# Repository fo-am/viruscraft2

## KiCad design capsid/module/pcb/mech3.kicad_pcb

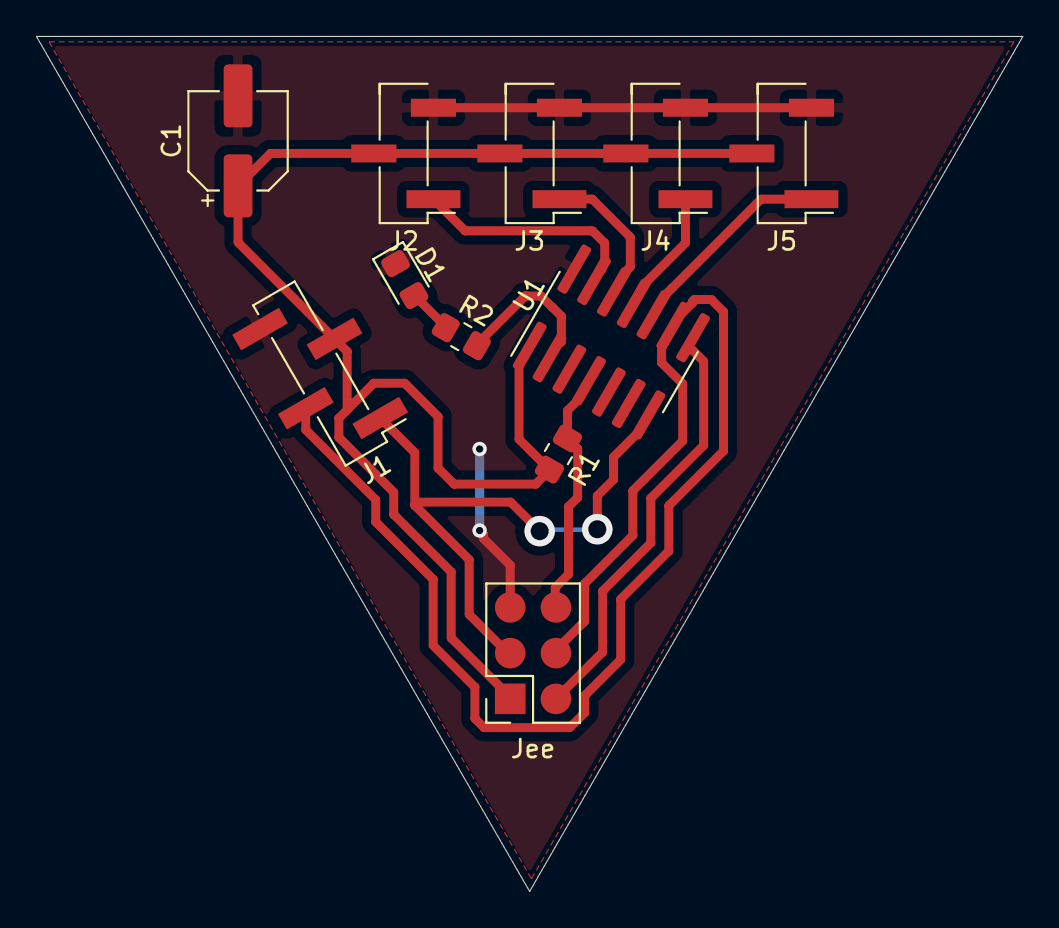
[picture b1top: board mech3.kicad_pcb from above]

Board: 2 copper layers, 54.8 x 47.5 mm, 11 parts (0 on the bottom side), 12 nets.

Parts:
C1: 120uF; CP_Elec_5x5.8
D1: LED; LED_0805_2012Metric_Pad1.15x1.40mm_HandSolder
J1: Conn_01x04_Male; PinHeader_1x04_P2.54mm_Vertical_SMD_Pin1Left
J2, J3, J4, J5: Conn_01x03_Male; PinHeader_1x03_P2.54mm_Vertical_SMD_Pin1Left
Jee: Conn_02x03_Odd_Even; PinSocket_2x03_P2.54mm_Vertical
R1: 10K; R_0805_2012Metric_Pad1.20x1.40mm_HandSolder
R2: 100; R_0805_2012Metric_Pad1.20x1.40mm_HandSolder
U1: ATtiny84A-SSU; SOIC-14_3.9x8.7mm_P1.27mm

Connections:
+5V: C1.1, J1.3, J2.2, J3.2, J4.2, J5.2, Jee.1, R1.2, U1.1
/miso: Jee.2, U1.8
/reset: Jee.6, R1.1, U1.4
/scl: J1.2, Jee.4, U1.9
/sda: J1.1, Jee.3, U1.7
/servo_a: J2.1, U1.13
/servo_b: J3.1, U1.12
/servo_c: J4.1, U1.11
/servo_d: J5.1, U1.10
Earth: C1.2, D1.1, J1.4, J2.3, J3.3, J4.3, J5.3, Jee.5, U1.14
unnamed: D1.2, R2.1
unnamed: R2.2, U1.2

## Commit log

2020-10-20 first commit - working avr servo controller
2020-10-20 added arduino prototype
2020-10-20 rename
2020-10-20 mess
2020-10-20 added mech design
2020-10-23 new registers
2020-12-01 working version on PCB
2020-12-01 update kicad files
2021-01-12 new game code started
2021-01-12 removed old screenshots
2021-01-14 added hosts and fluid sim
2021-01-15 basic infection
2021-01-16 swapped virus host ownership so the host takes control of the virus when it's infected
2021-01-18 random optimisations
2021-01-20 first playable version
2021-01-21 made more playable, and a bit hard
2021-01-21 text
2021-02-10 micro viruses
2021-02-18 added levels to the game
2021-02-22 levels added and tuned
2021-02-22 params from browser
2021-02-23 added mutation game
2021-02-25 three receptors, tuning and fixes
2021-03-09 new host images, refactor to support multiple variants
2021-03-09 two new stages added
2021-03-09 hosts move better, levels balanced
2021-03-10 new host frames
2021-03-11 fixed host anim sequence and started stage implementation
2021-03-11 fading hosts
2021-03-11 small fix
2021-03-11 loading params fix
2021-03-11 maybe fix
2021-03-29 big commit with new host animations, receptors and viruses
2021-03-29 styling
2021-04-01 firmware improvements and working with dfrobot servos
2021-04-08 added arduino code and new mutator buttons
2021-04-08 buttons link to receptor mixer
2021-04-08 mixer now controls mutator button levels
2021-04-08 mixer behaves more as expected
2021-04-08 dice working
2021-04-08 dice better anim
2021-04-08 tweaks and simplifications - made the mutation just random, not a 50% chance of changing a receptor
2021-04-08 added favicon
2021-04-10 added a scoring system and hints
2021-04-10 only one tip at a time!
2021-04-10 added help bubbles - no actual help yet tho
2021-04-12 added servo driver
2021-04-12 added bad sensor code
2021-04-12 added non-debug params mode Fixed: #11
2021-04-12 jigging around the draw order and added lives Fixed: #17
2021-04-13 linked stages and levels together Fixed: #4
2021-04-13 text bg Fixed: #25
2021-04-13 removed mutation countdown when it's not gonna happen before the level ind Fixed: #21
2021-04-13 Increased grace amount of hosts before infection can occur to 3 Fixed: #24
2021-04-13 started score saving and server work Fixed: #28 Fixed: #27
2021-04-13 sorted scoring, database and leaderboard Fixed: #29 Fixed: #6
2021-04-13 turned off cheat
2021-04-13 added missing help bubbles
2021-04-13 loading text col
2021-04-13 nuking old local parameters
2021-04-14 swapped multivariant mutator for the shape buttons Fixed: #33
2021-04-15 added help for first stage Fixed: #32 Fixed: #22
2021-04-15 help fix
2021-04-15 more help text
2021-04-15 Fixed: #31
2021-04-27 6 triangles working
2021-05-07 added calibration to the capsid driver and tested a load of servos
2021-05-07 tested new pcb and added power control to the driver
2021-05-10 added server for robot control
2021-05-10 game now talks to the robot
2021-05-12 all triangle test & added auto reboot
2021-05-13 virus WORKING, added crc checks and fine tuning timing
2021-05-13 firmware updates, watchdog timers, crc checking, brownout fuse set...
2021-05-20 added auto detection, crc and everything to shape server
2021-05-20 new calibration to stop it overpowering, and a lot of tweaking
2021-05-21 page navigation and structure expanded - Fixed: #48
2021-05-21 new buttons added Fixed: #46
2021-05-21 help bubbles now use highlight col
2021-05-21 added question marks to virus in hidden game: Fixed: #40 Fixed: #1
2021-05-21 sprites now have 1 pixel overlap, seems to help with joins - Fixed: #41
2021-05-21 another 1 pixel overlap fix
2021-05-21 added demo hosts
2021-05-24 added viruses to the demo - Fixed: #11
2021-05-24 added sensor hardware
2021-05-24 added cheat mode
2021-05-26 new IP addr
2021-05-26 added sensor websocket thingy and tests all working
2021-05-27 fixed demo problem when not registered, and reordered buttons
2021-05-27 sorting out installation-version
2021-06-04 added about text, game over condition, added game end screen, added score for ranking Fixed: #30
2021-06-04 leaderboard and end game sorted
2021-06-04 fixed play again button
2021-06-04 added arrow to help boxes Fixed: #50
2021-06-04 more help bubbles Fixed: #43 Fixed: #36
2021-06-04 loads more tips, and more positive when doing well! Fixed: #42
2021-06-04 added decent about (first pass) Fixed: #39 Fixed: #8
2021-06-04 added bens stuff Fixed: #64
2021-06-04 added logos Fixed: #63
2021-06-04 bumped params version just in case
2021-06-04 cleaned up keyboard
2021-06-04 full o typos
2021-06-04 simplified results page - Fixed: #71
2021-06-04 fixed/clamped host turning Fixed: #68
2021-06-04 made demo virus a bit smaller Fixed: #67
2021-06-04 banners and pluralising Fixed: #70
2021-06-04 fixed end game thing and turned off cheating
2021-06-04 quit help button tweak Fixed: #72
2021-06-18 added sounds
2021-06-21 server ip address now fixed
2021-06-23 installation mode setup Fixed: #57
2021-06-24 added end of stage text Fixed: #78
2021-06-24 added apostrophe Fixed: #77
2021-06-24 messing with ben's page Fixed: #76 Fixed: #75
2021-06-24 fixed virus spacing Fixed: #73
2021-06-24 restart on tab hide Fixed: #18
2021-06-24 privacy wording and opt out button Fixed: #15
2021-06-24 added cheat mode Fixed: #80
2021-06-24 fixed shape distribution when number of triangles is odd
2021-06-24 added missing image
2021-06-24 debouncing sensor buttons
2021-06-24 added shutdown - Fixed: #81
2021-06-25 tweaked positioning of shape buttons on online version Fixed: #45
2021-06-25 filtered sensor inputs Fixed: #82
2021-06-25 turned off installation
2021-07-05 added hand+boxes Fixed: #86 Fixed: #85
2021-07-05 typo Fixed: #83
2021-07-05 sorted logos Fixed: #69
2021-07-05 more about and text fixes
2021-07-05 popup fixes Fixed: #74
2021-07-07 removed eeprom reading and added docs
2021-07-13 added robot test to secrets page
2021-07-13 added server reset to the menu
2021-08-13 auto restarting sensors when their i2c comms fail - and set to wifi for testing
2021-08-23 sensor firmware fix
2021-08-31 added device scanning for secrets page, sensors clear reload timeout, sensor check sped up
2021-10-18 added more help - closes: #91
2021-10-18 tweaked gdpr text and closed: #90
2021-11-11 removed weekly scores and made game slightly harder
2021-11-11 removed final level end
2021-11-11 sensor error fix
